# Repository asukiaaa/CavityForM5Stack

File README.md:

# M5StackCavity

PCBs to create a cavity for M5Stack.

# License

MIT

# References

- [M5StackCavity ピンソケット、ブレッドボード無し](https://www.switch-science.com/catalog/5684/)
- [M5StackCavity ピンソケット、ブレッドボード付き](https://www.switch-science.com/catalog/5685/)
- [M5StackのStackに背の高い部品を利用できるM5StackCavityを作ってみた](http://asukiaaa.blogspot.com/2019/08/m5stackstackm5stackcavity.html)

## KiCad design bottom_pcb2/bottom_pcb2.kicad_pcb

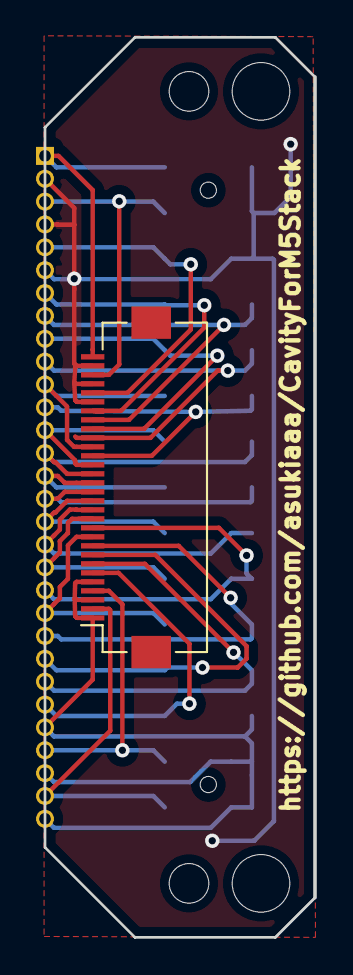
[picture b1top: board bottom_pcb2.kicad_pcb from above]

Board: 2 copper layers, 15.0 x 50.0 mm, 7 parts (1 on the bottom side), 26 nets.

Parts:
J1: socket; PinSocket_2x15_P2.54mm_Vertical_SMD_just_for_M5Stack_bottom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
J3: free_holes; PinHeader_1x30_P1.27mm_Vertical_without_silks
Jv: flat_cable_connector; Hirose_FH12-30S-0.5SH_1x30-1MP_P0.50mm_Horizontal
REF3, REF8: MountingHole_2.2mm_M2
REF4, REF9: MountingHole_3.2mm_M3

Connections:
+3V3: J1.11, J3.11, Jv.20
+5V: J1.27, J3.27, Jv.4
+BATT: J1.29, J3.29, Jv.2
G0: J1.23, J3.23, Jv.8
G1: J1.13, J3.13, Jv.18
G2: J1.20, J3.20, Jv.11
G3: J1.14, J3.14, Jv.17
G5: J1.19, J3.19, Jv.12
G12: J1.22, J3.22, Jv.9
G13: J1.21, J3.21, Jv.10
G15: J1.24, J3.24, Jv.7
G16: J1.16, J3.16, Jv.15
G17: J1.15, J3.15, Jv.16
G18: J1.12, J3.12, Jv.19
G19: J1.10, J3.10, Jv.21
G21: J1.18, J3.18, Jv.13
G22: J1.17, J3.17, Jv.14
G23: J1.8, J3.8, Jv.23
G25: J1.7, J3.7, Jv.24
G26: J1.9, J3.9, Jv.22
G34: J1.25, J3.25, Jv.6
G35: J1.1, J3.1, Jv.30
G36: J1.3, J3.3, Jv.28
GND: J1.2, J1.4, J1.6, J3.2, J3.4, J3.6, Jv.25, Jv.27, Jv.29
HPWR: J1.26, J1.28, J1.30, J3.26, J3.28, J3.30, Jv.1, Jv.3, Jv.5
RST: J1.5, J3.5, Jv.26

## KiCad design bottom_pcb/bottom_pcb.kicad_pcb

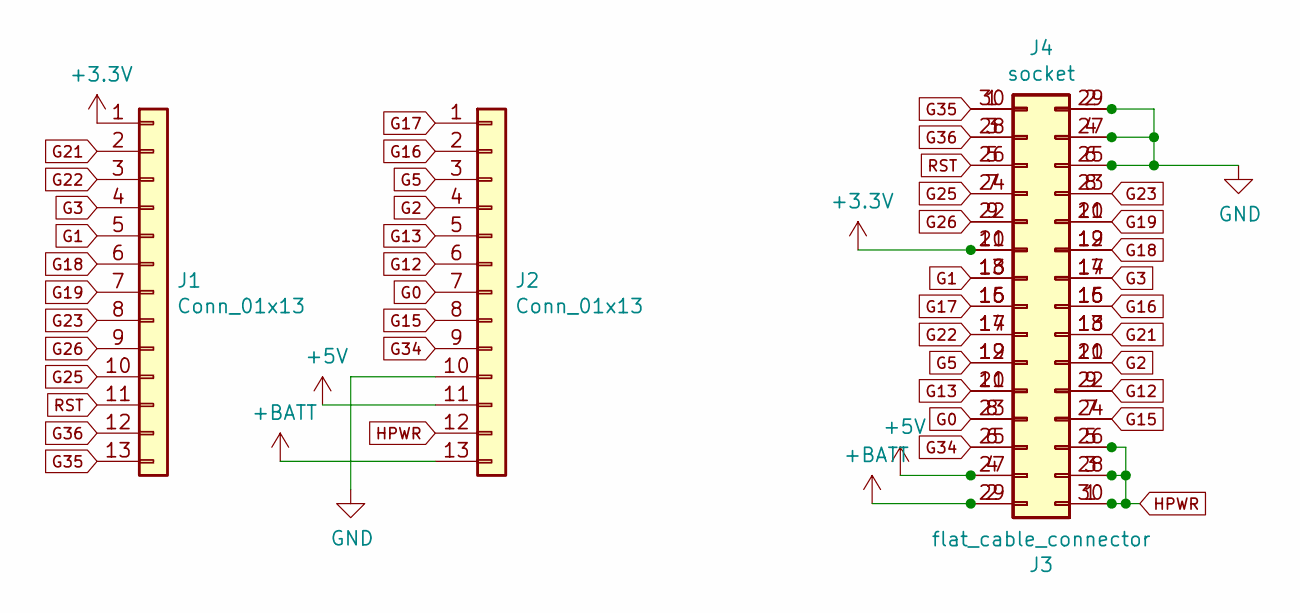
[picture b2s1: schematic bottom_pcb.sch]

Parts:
J1, J2: Conn_01x13; PinSocket_1x13_P2.54mm_Vertical_without_silks
J3: flat_cable_connector; Hirose_FH12-30S-0.5SH_1x30-1MP_P0.50mm_Horizontal
J4: socket; PinSocket_2x15_P2.54mm_Vertical_SMD_just_for_M5Stack_bottom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

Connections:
+3V3: J1.1, J3.20, J4.11
+5V: J2.11, J3.4, J4.27
+BATT: J2.13, J3.2, J4.29
G0: J2.7, J3.8, J4.23
G1: J1.5, J3.18, J4.13
G2: J2.4, J3.11, J4.20
G3: J1.4, J3.17, J4.14
G5: J2.3, J3.12, J4.19
G12: J2.6, J3.9, J4.22
G13: J2.5, J3.10, J4.21
G15: J2.8, J3.7, J4.24
G16: J2.2, J3.15, J4.16
G17: J2.1, J3.16, J4.15
G18: J1.6, J3.19, J4.12
G19: J1.7, J3.21, J4.10
G21: J1.2, J3.13, J4.18
G22: J1.3, J3.14, J4.17
G23: J1.8, J3.23, J4.8
G25: J1.10, J3.24, J4.7
G26: J1.9, J3.22, J4.9
G34: J2.9, J3.6, J4.25
G35: J1.13, J3.30, J4.1
G36: J1.12, J3.28, J4.3
GND: J2.10, J3.25, J3.27, J3.29, J4.2, J4.4, J4.6
HPWR: J2.12, J3.1, J3.3, J3.5, J4.26, J4.28, J4.30
RST: J1.11, J3.26, J4.5

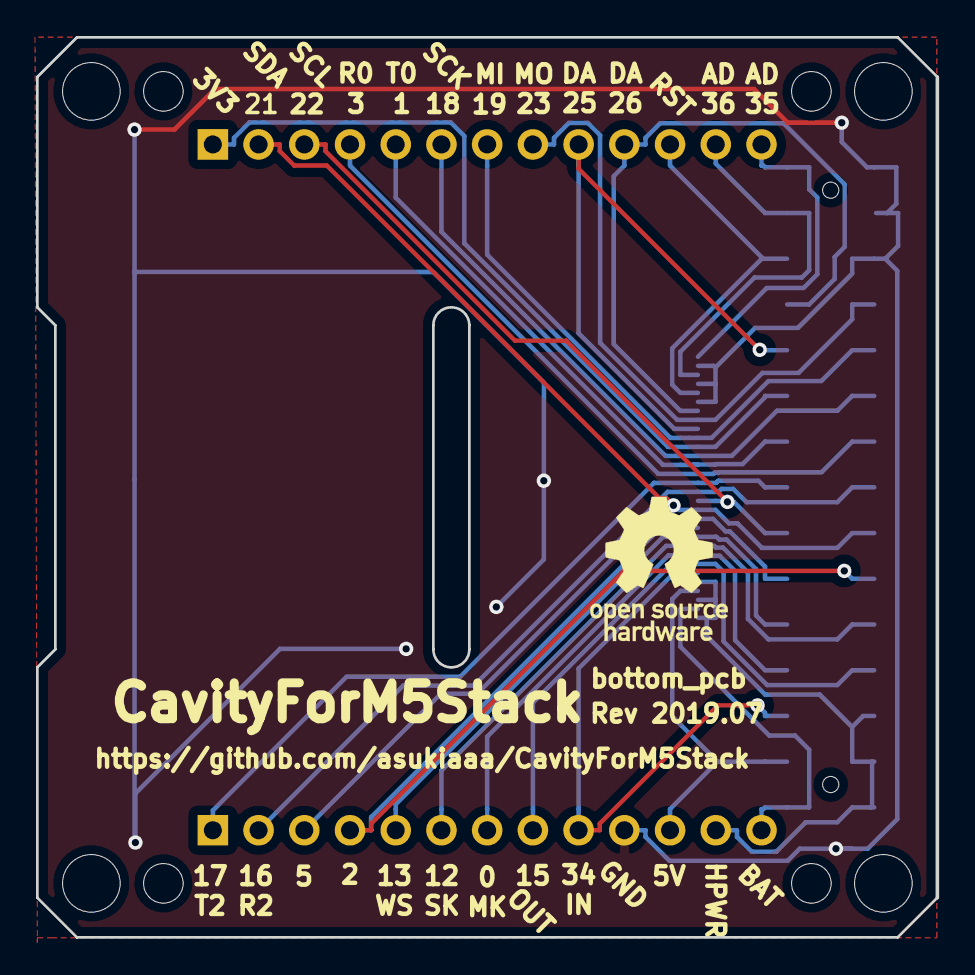
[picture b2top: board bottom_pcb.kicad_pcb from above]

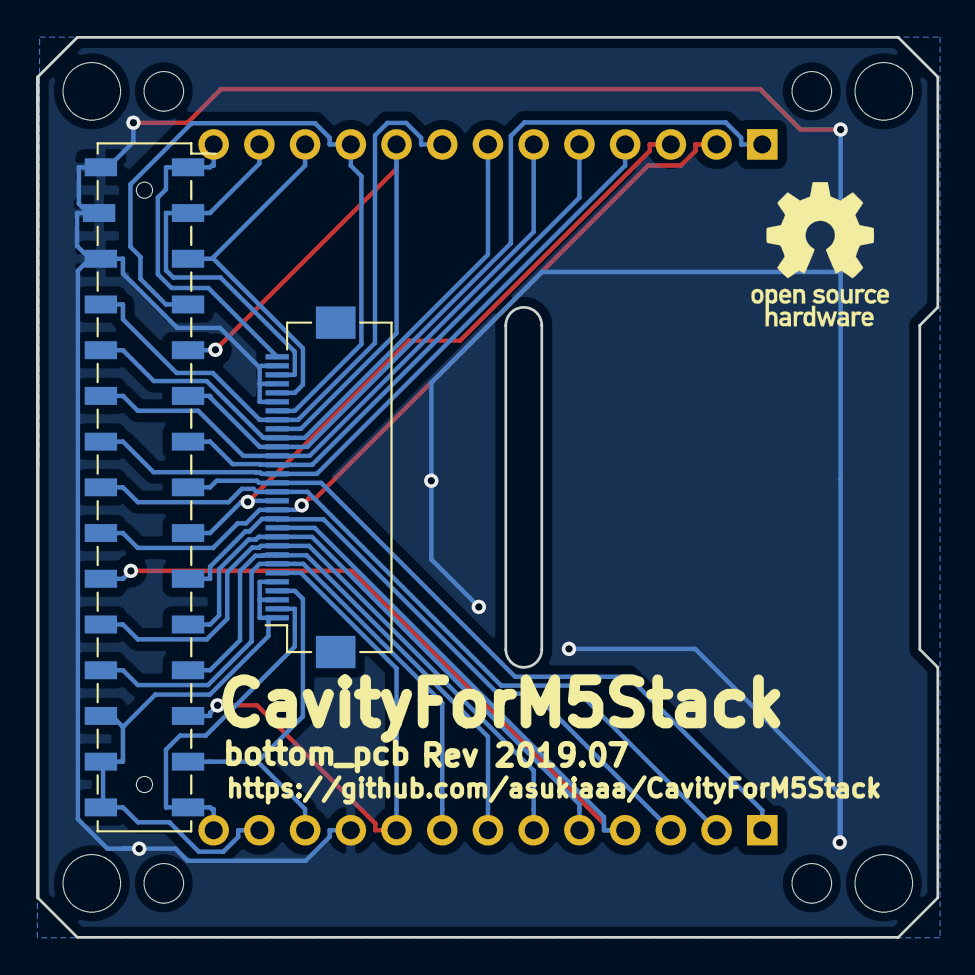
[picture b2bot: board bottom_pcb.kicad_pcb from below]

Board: 2 copper layers, 50.0 x 50.0 mm, 14 parts (3 on the bottom side), 26 nets.

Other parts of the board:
OSHWREF1, OSHWREF2: OSHW-Logo_7.5x8mm_SilkScreen
REF1, REF4, REF6, REF9: MountingHole_3.2mm_M3
REF2, REF3, REF7, REF8: MountingHole_2.2mm_M2

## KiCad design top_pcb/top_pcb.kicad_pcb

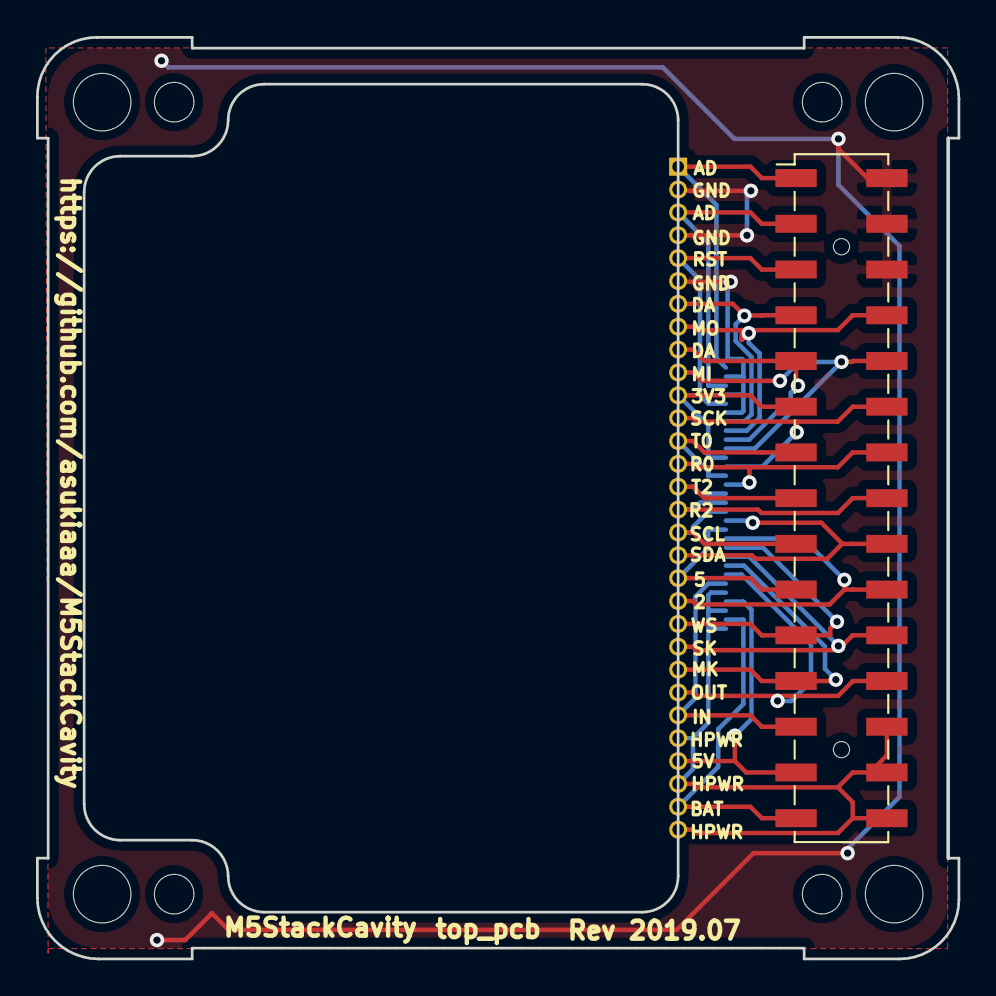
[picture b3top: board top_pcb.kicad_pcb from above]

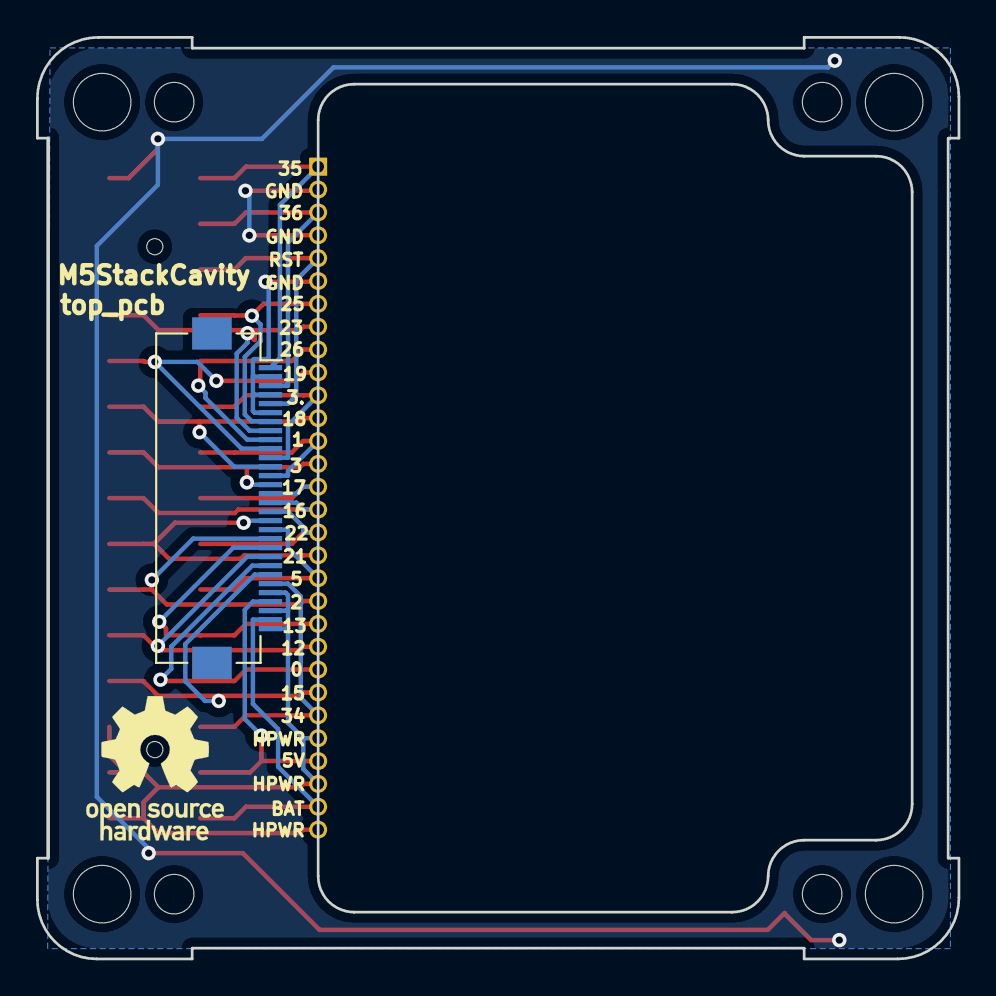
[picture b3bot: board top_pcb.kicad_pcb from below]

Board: 2 copper layers, 51.2 x 51.2 mm, 16 parts (2 on the bottom side), 26 nets.

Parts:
J1: flat_cable_connector; Hirose_FH12-30S-0.5SH_1x30-1MP_P0.50mm_Horizontal
J2: header; PinHeader_2x15_P2.54mm_Vertical_SMD_for_M5Stack
J3: free_holes; PinHeader_1x30_P1.27mm_Vertical_without_silks
OSHWREF2: OSHW-Logo_7.5x8mm_SilkScreen
REF1, REF4, REF6, REF9: MountingHole_3.2mm_M3
REF2, REF3, REF7, REF8: MountingHole_2.2mm_M2
corner1, corner4: corner_edge1
corner2, corner3: corner_edge2

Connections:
+3V3: J1.11, J2.11, J3.11
+5V: J1.27, J2.27, J3.27
+BATT: J1.29, J2.29, J3.29
G0: J1.23, J2.23, J3.23
G1: J1.13, J2.13, J3.13
G2: J1.20, J2.20, J3.20
G3: J1.14, J2.14, J3.14
G5: J1.19, J2.19, J3.19
G12: J1.22, J2.22, J3.22
G13: J1.21, J2.21, J3.21
G15: J1.24, J2.24, J3.24
G16: J1.16, J2.16, J3.16
G17: J1.15, J2.15, J3.15
G18: J1.12, J2.12, J3.12
G19: J1.10, J2.10, J3.10
G21: J1.18, J2.18, J3.18
G22: J1.17, J2.17, J3.17
G23: J1.8, J2.8, J3.8
G25: J1.7, J2.7, J3.7
G26: J1.9, J2.9, J3.9
G34: J1.25, J2.25, J3.25
G35: J1.1, J2.1, J3.1
G36: J1.3, J2.3, J3.3
GND: J1.2, J1.4, J1.6, J2.2, J2.4, J2.6, J3.2, J3.4, J3.6
HPWR: J1.26, J1.28, J1.30, J2.26, J2.28, J2.30, J3.26, J3.28, J3.30
RST: J1.5, J2.5, J3.5

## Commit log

2019-05-29 Add space for flat cable to bottom pcb
2019-05-29 Add license info
2019-06-01 Change connector position on top_pcb
2019-06-23 Assign corner edge to top_pcb
2019-06-23 Add hole to top_pcb
2019-06-23 Update gerber files
2019-06-23 Add fp-info-cache to .gitignore
2019-07-09 Update center connector position on bottom_pcb
2019-07-09 Add fp-info-cache to .gitignore of bottom_pcb
2019-07-12 Add center hole to bottom_pcb
2019-07-12 Remove redundant footprints from top_pcb
2019-07-12 Change pad size smaller for pin socket on top_pcb
2019-07-12 Export gerber files to order rev 2019.07
2019-07-12 Add bom.csv
2019-07-12 Add requirements
2019-08-24 Add pinsockets to bom
2019-08-24 Add image to readme
2019-08-24 Add product and blog link to readme
2019-11-03 Rename project name to CavityForM5Stack from M5StackCavity
2020-03-04 Add bottom_pcb2
2020-03-04 Remove redundant gerber files for bottom_pcb and top_pcb
2020-03-04 Change label layer for bottom_pcb2
